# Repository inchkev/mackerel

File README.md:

# mackerel

mackerel is a 58 key (6x4+5 split) column-staggered choc-spaced split ergonomic keyboard. mackerel is a successor to [calico](https://github.com/inchkev/calico), my first split keyboard.

- rp2040-zero based
- reversible pcb

## board

## to build mackerel, you'll need:

* 2x mackerel pcbs
* 2x waveshare rp2040-zero or similar
* 58x choc v1 switches
* 58x choc 1u keycaps (I used MBK profile)
* 58x Kailh choc hotswap sockets
* 58x SOD-123 diodes (I used 1N4148W)
* 2x TRRS PJ-320A jacks
* 1x TRRS cable
* 1x usb-c cable
* 3d printed enclosure (wip...)

## mackerel was inspired by

* [calico](https://github.com/inchkev/calico) and all its inspirations
* [pluckey by floookay](https://github.com/floookay/pluckey)
* [TOTEM by GEIGEIGEIST](https://github.com/GEIGEIGEIST/TOTEM)

### and licensed under

[CERN-OHL-W-2.0](https://spdx.org/licenses/CERN-OHL-W-2.0.html) overall. mackerel uses footprints, modified and unmodified, under different licenses. see [ATTRIBUTIONS.md](ATTRIBUTIONS.md).

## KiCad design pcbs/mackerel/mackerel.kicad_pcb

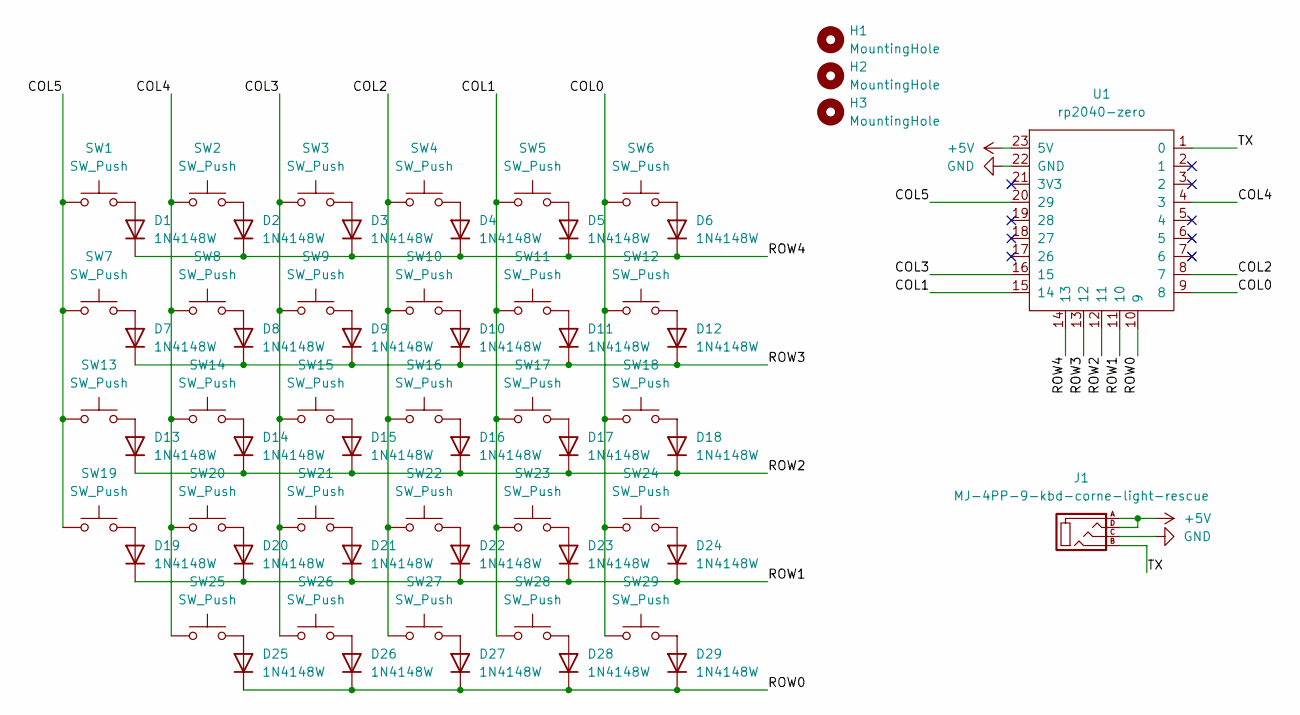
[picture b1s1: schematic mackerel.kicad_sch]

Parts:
D1, D2, D3, D4, D5, D6, D7, D8, D9, D10, D11, D12, D13, D14, D15, D16, D17, D18, D19, D20, D21, D22, D23, D24, D25, D26, D27, D28, D29: 1N4148W; D3_SMD_modified
H1, H2, H3: MountingHole
J1: MJ-4PP-9-kbd-corne-light-rescue; TRRS-3pin_modified
SW1, SW2, SW3, SW4, SW5, SW6, SW7, SW8, SW9, SW10, SW11, SW12, SW13, SW14, SW15, SW16, SW17, SW18, SW19, SW20, SW21, SW22, SW23, SW24, SW25, SW26, SW27, SW28, SW29: SW_Push; Kailh_socket_PG1350_reversible
U1: rp2040-zero; rp2040-zero-tht_modified-semi-reversible

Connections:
+5V: J1.A, J1.D, U1.23 (5V)
/COL0: SW6.1, SW12.1, SW18.1, SW24.1, SW29.1, U1.9 (8)
/COL1: SW5.1, SW11.1, SW17.1, SW23.1, SW28.1, U1.15 (14)
/COL2: SW4.1, SW10.1, SW16.1, SW22.1, SW27.1, U1.8 (7)
/COL3: SW3.1, SW9.1, SW15.1, SW21.1, SW26.1, U1.16 (15)
/COL4: SW2.1, SW8.1, SW14.1, SW20.1, SW25.1, U1.4 (3)
/COL5: SW1.1, SW7.1, SW13.1, SW19.1, U1.20 (29)
/ROW0: D25.1 (K), D26.1 (K), D27.1 (K), D28.1 (K), D29.1 (K), U1.10 (9)
/ROW1: D19.1 (K), D20.1 (K), D21.1 (K), D22.1 (K), D23.1 (K), D24.1 (K), U1.11 (10)
/ROW2: D13.1 (K), D14.1 (K), D15.1 (K), D16.1 (K), D17.1 (K), D18.1 (K), U1.12 (11)
/ROW3: D7.1 (K), D8.1 (K), D9.1 (K), D10.1 (K), D11.1 (K), D12.1 (K), U1.13 (12)
/ROW4: D1.1 (K), D2.1 (K), D3.1 (K), D4.1 (K), D5.1 (K), D6.1 (K), U1.14 (13)
/TX: J1.B, U1.1 (0)
GND: J1.C, U1.22 (GND)
unnamed: D1.2 (A), SW1.2
unnamed: D2.2 (A), SW2.2
unnamed: D3.2 (A), SW3.2
unnamed: D4.2 (A), SW4.2
unnamed: D5.2 (A), SW5.2
unnamed: D6.2 (A), SW6.2
unnamed: D7.2 (A), SW7.2
unnamed: D8.2 (A), SW8.2
unnamed: D9.2 (A), SW9.2
unnamed: D10.2 (A), SW10.2
unnamed: D11.2 (A), SW11.2
unnamed: D12.2 (A), SW12.2
unnamed: D13.2 (A), SW13.2
unnamed: D14.2 (A), SW14.2
unnamed: D15.2 (A), SW15.2
unnamed: D16.2 (A), SW16.2
unnamed: D17.2 (A), SW17.2
unnamed: D18.2 (A), SW18.2
unnamed: D19.2 (A), SW19.2
unnamed: D20.2 (A), SW20.2
unnamed: D21.2 (A), SW21.2
unnamed: D22.2 (A), SW22.2
unnamed: D23.2 (A), SW23.2
unnamed: D24.2 (A), SW24.2
unnamed: D25.2 (A), SW25.2
unnamed: D26.2 (A), SW26.2
unnamed: D27.2 (A), SW27.2
unnamed: D28.2 (A), SW28.2
unnamed: D29.2 (A), SW29.2

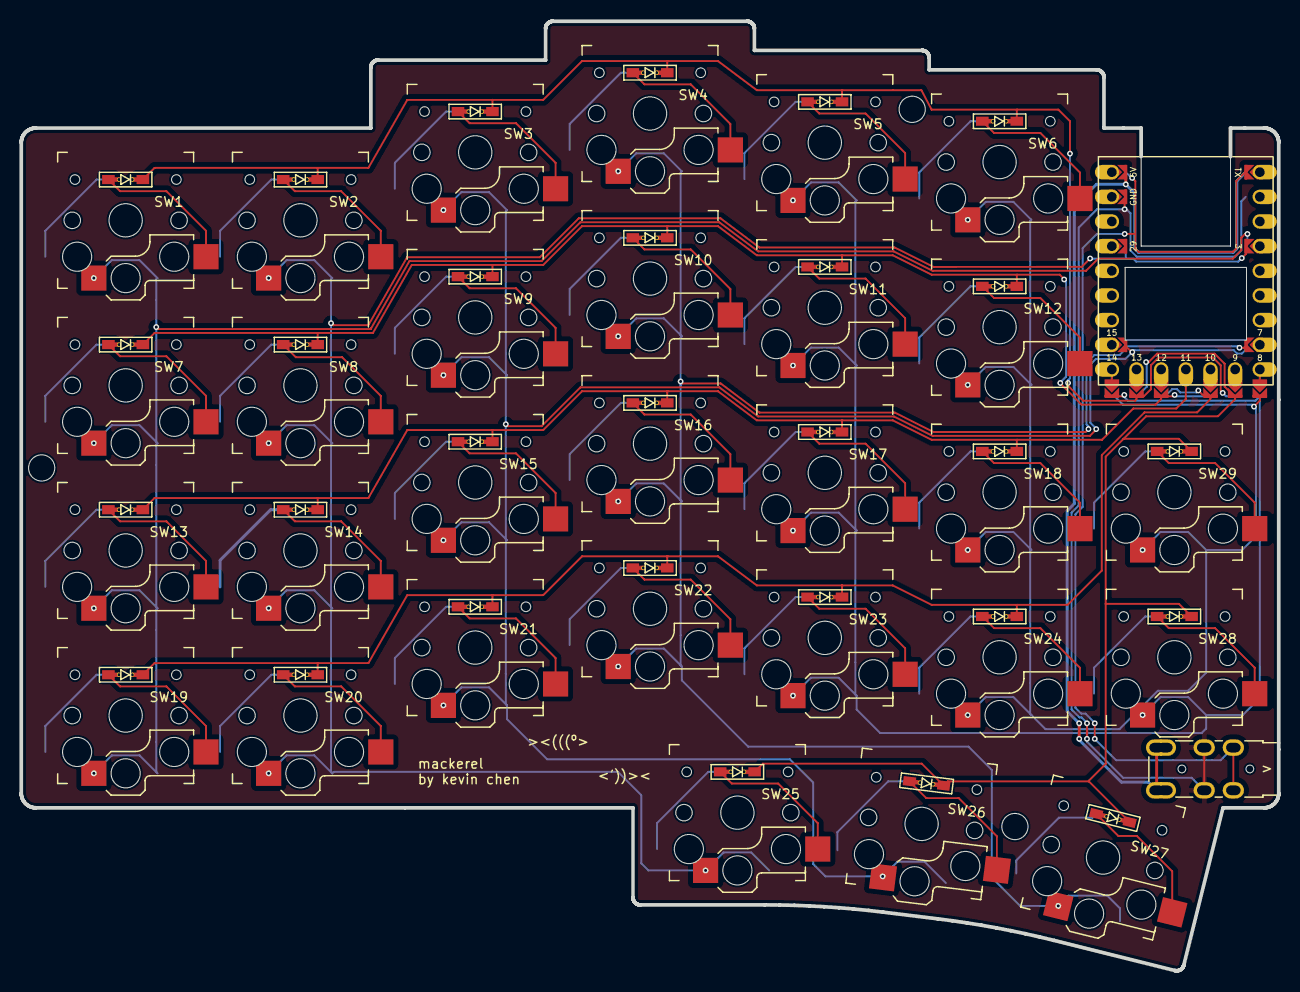
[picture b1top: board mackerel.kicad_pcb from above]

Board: 2 copper layers, 129.5 x 97.8 mm, 60 parts (0 on the bottom side), 43 nets.

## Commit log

2025-05-29 licenses
2025-05-29 remove README
2025-05-29 touchup
2025-05-29 attributions
